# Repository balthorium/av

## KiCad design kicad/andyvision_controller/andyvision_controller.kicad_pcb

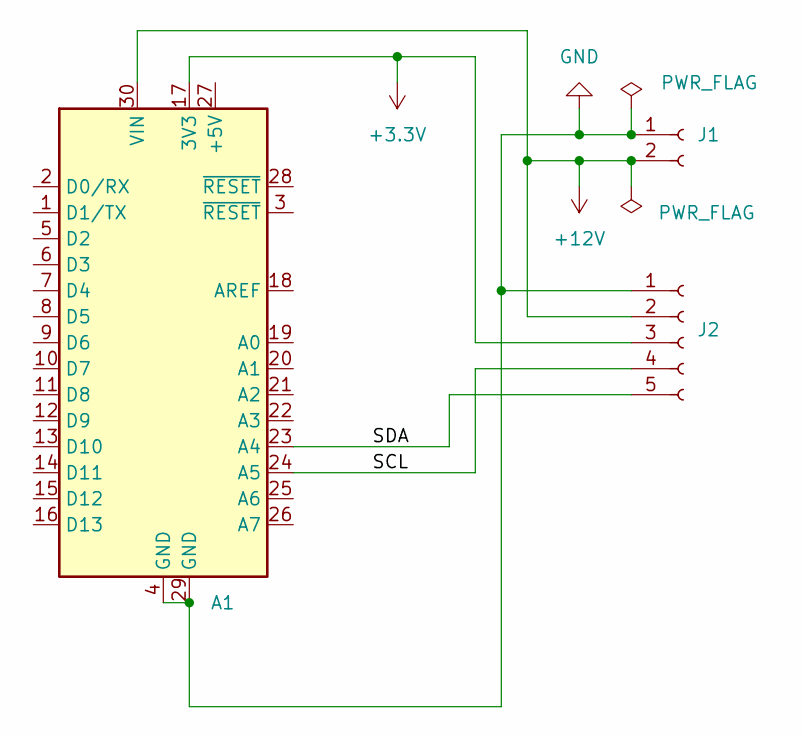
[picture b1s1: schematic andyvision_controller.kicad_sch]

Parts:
A1: Arduino_Nano_v3.x; Arduino_Nano
J1: Conn_01x02_Female; JST_XH_B2B-XH-A_1x02_P2.50mm_Vertical
J2: Conn_01x05_Female; JST_XH_B5B-XH-A_1x05_P2.50mm_Vertical

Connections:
+3.3V: A1.17 (3V3), J2.3
+12V: A1.30 (VIN), J1.2, J2.2
/SCL: A1.24 (A5), J2.4
/SDA: A1.23 (A4), J2.5
GND: A1.4 (GND), A1.29 (GND), J1.1, J2.1

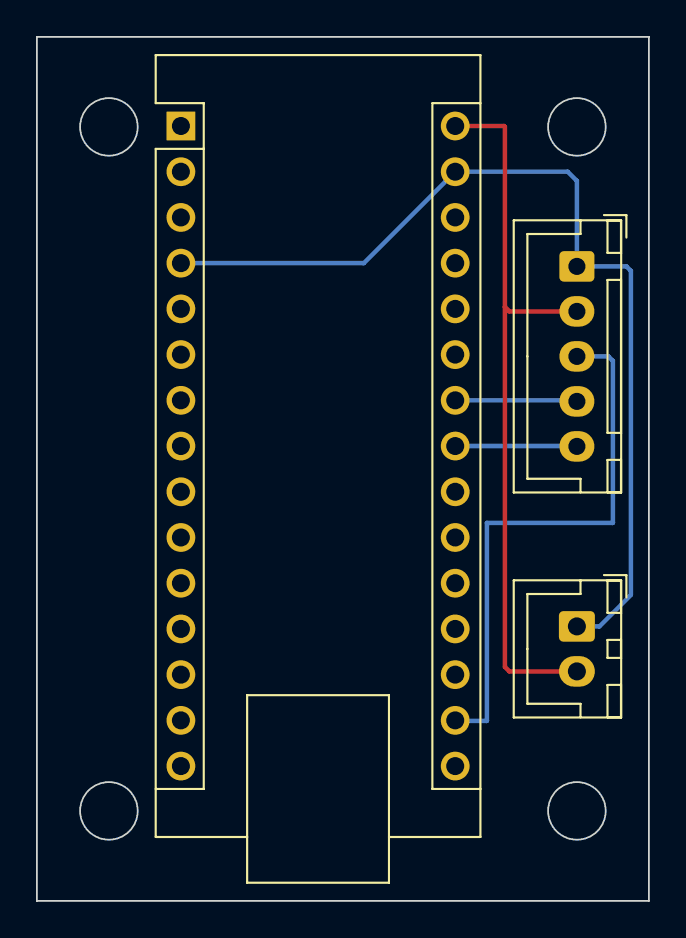
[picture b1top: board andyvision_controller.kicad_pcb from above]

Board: 2 copper layers, 34.0 x 48.0 mm, 3 parts (0 on the bottom side), 5 nets.

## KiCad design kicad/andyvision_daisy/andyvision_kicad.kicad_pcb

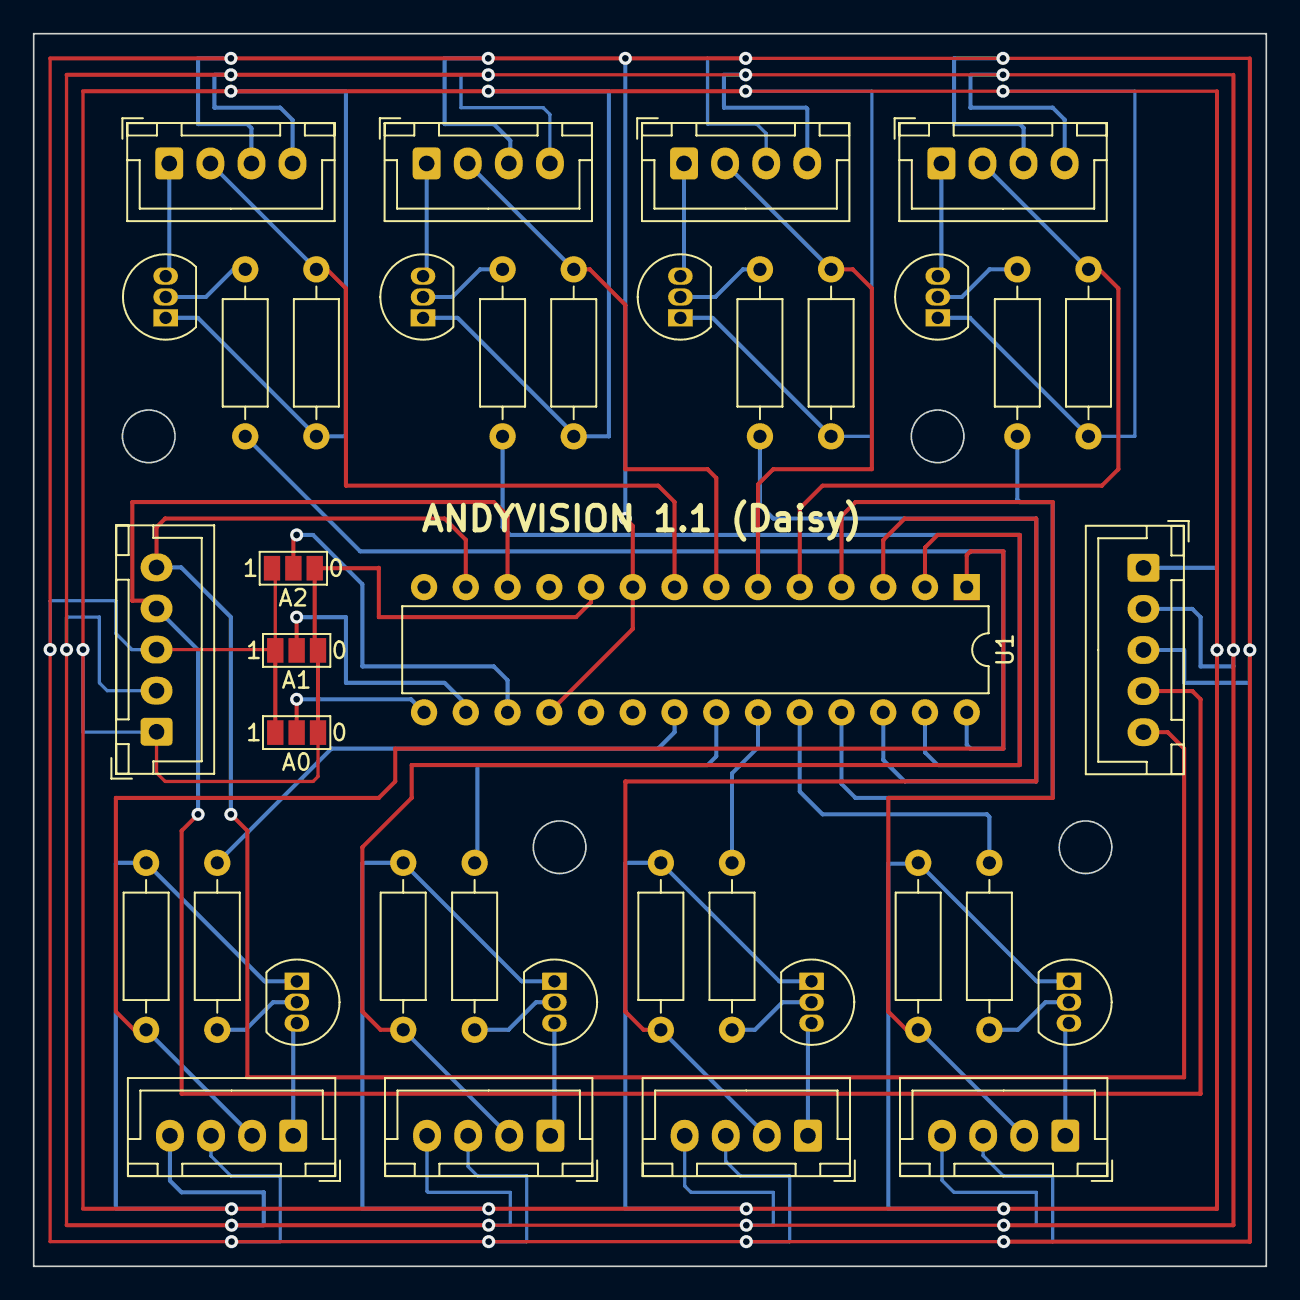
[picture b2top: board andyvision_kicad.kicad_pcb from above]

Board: 2 copper layers, 75.0 x 75.0 mm, 38 parts (0 on the bottom side), 40 nets.

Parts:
A0, A1, A2: Jumper_3; SolderJumper-3_P1.3mm_Open_Pad1.0x1.5mm_NumberLabels
J1, J2: Conn_01x05_Female; JST_XH_B5B-XH-A_1x05_P2.50mm_Vertical
J3, J4, J5, J6, J7, J8, J9, J10: Conn_01x04_Female; JST_XH_B4B-XH-A_1x04_P2.50mm_Vertical
Q1, Q2, Q3, Q4, Q5, Q6, Q7, Q8: PN2222A; TO-92_Inline
R1, R2, R3, R4, R5, R6, R7, R8, R9, R10, R11, R12, R13, R14, R15, R16: R; R_Axial_DIN0207_L6.3mm_D2.5mm_P10.16mm_Horizontal
U1: MCP23017_SP; DIP-28_W7.62mm

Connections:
+5V: A0.3 (B), A1.3 (B), A2.3 (B), J1.3, J2.3, J3.3, J4.3, J5.3, J6.3, J7.3, J8.3, J9.3, J10.3, U1.9 (VDD), U1.18 (~RESET)
+12V: J1.2, J2.2, J3.4, J4.4, J5.4, J6.4, J7.4, J8.4, J9.4, J10.4
/daisy/JPB9/DIG IN: J3.2, R1.2, U1.8 (GPB7)
/daisy/JPB9/DIG OUT: R2.2, U1.28 (GPA7)
/daisy/JPB10/DIG IN: J4.2, R3.2, U1.7 (GPB6)
/daisy/JPB10/DIG OUT: R4.2, U1.27 (GPA6)
/daisy/JPB11/DIG IN: J6.2, R7.2, U1.5 (GPB4)
/daisy/JPB11/DIG OUT: R8.2, U1.25 (GPA4)
/daisy/JPB12/DIG IN: J5.2, R5.2, U1.6 (GPB5)
/daisy/JPB12/DIG OUT: R6.2, U1.26 (GPA5)
/daisy/JPB13/DIG IN: J9.2, R13.2, U1.2 (GPB1)
/daisy/JPB13/DIG OUT: R14.2, U1.22 (GPA1)
/daisy/JPB14/DIG IN: J7.2, R9.2, U1.4 (GPB3)
/daisy/JPB14/DIG OUT: R10.2, U1.24 (GPA3)
/daisy/JPB15/DIG IN: J8.2, R11.2, U1.3 (GPB2)
/daisy/JPB15/DIG OUT: R12.2, U1.23 (GPA2)
/daisy/JPB16/DIG IN: J10.2, R15.2, U1.1 (GPB0)
/daisy/JPB16/DIG OUT: R16.2, U1.21 (GPA0)
/daisy/SCL: J1.4, J2.4, U1.12 (SCK)
/daisy/SDA: J1.5, J2.5, U1.13 (SDA)
GND: A0.1 (A), A1.1 (A), A2.1 (A), J1.1, J2.1, Q1.1 (E), Q2.1 (E), Q3.1 (E), Q4.1 (E), Q5.1 (E), Q6.1 (E), Q7.1 (E), Q8.1 (E), R1.1, R3.1, R5.1, R7.1, R9.1, R11.1, R13.1, R15.1, U1.10 (VSS)
unnamed: J3.1, Q1.3 (C)
unnamed: J4.1, Q2.3 (C)
unnamed: J5.1, Q3.3 (C)
unnamed: J6.1, Q4.3 (C)
unnamed: J7.1, Q5.3 (C)
unnamed: J8.1, Q6.3 (C)
unnamed: J9.1, Q7.3 (C)
unnamed: J10.1, Q8.3 (C)
unnamed: A2.2 (C), U1.17 (A2)
unnamed: A1.2 (C), U1.16 (A1)
unnamed: A0.2 (C), U1.15 (A0)
unnamed: Q1.2 (B), R2.1
unnamed: Q2.2 (B), R4.1
unnamed: Q3.2 (B), R6.1
unnamed: Q4.2 (B), R8.1
unnamed: Q5.2 (B), R10.1
unnamed: Q6.2 (B), R12.1
unnamed: Q7.2 (B), R14.1
unnamed: Q8.2 (B), R16.1
